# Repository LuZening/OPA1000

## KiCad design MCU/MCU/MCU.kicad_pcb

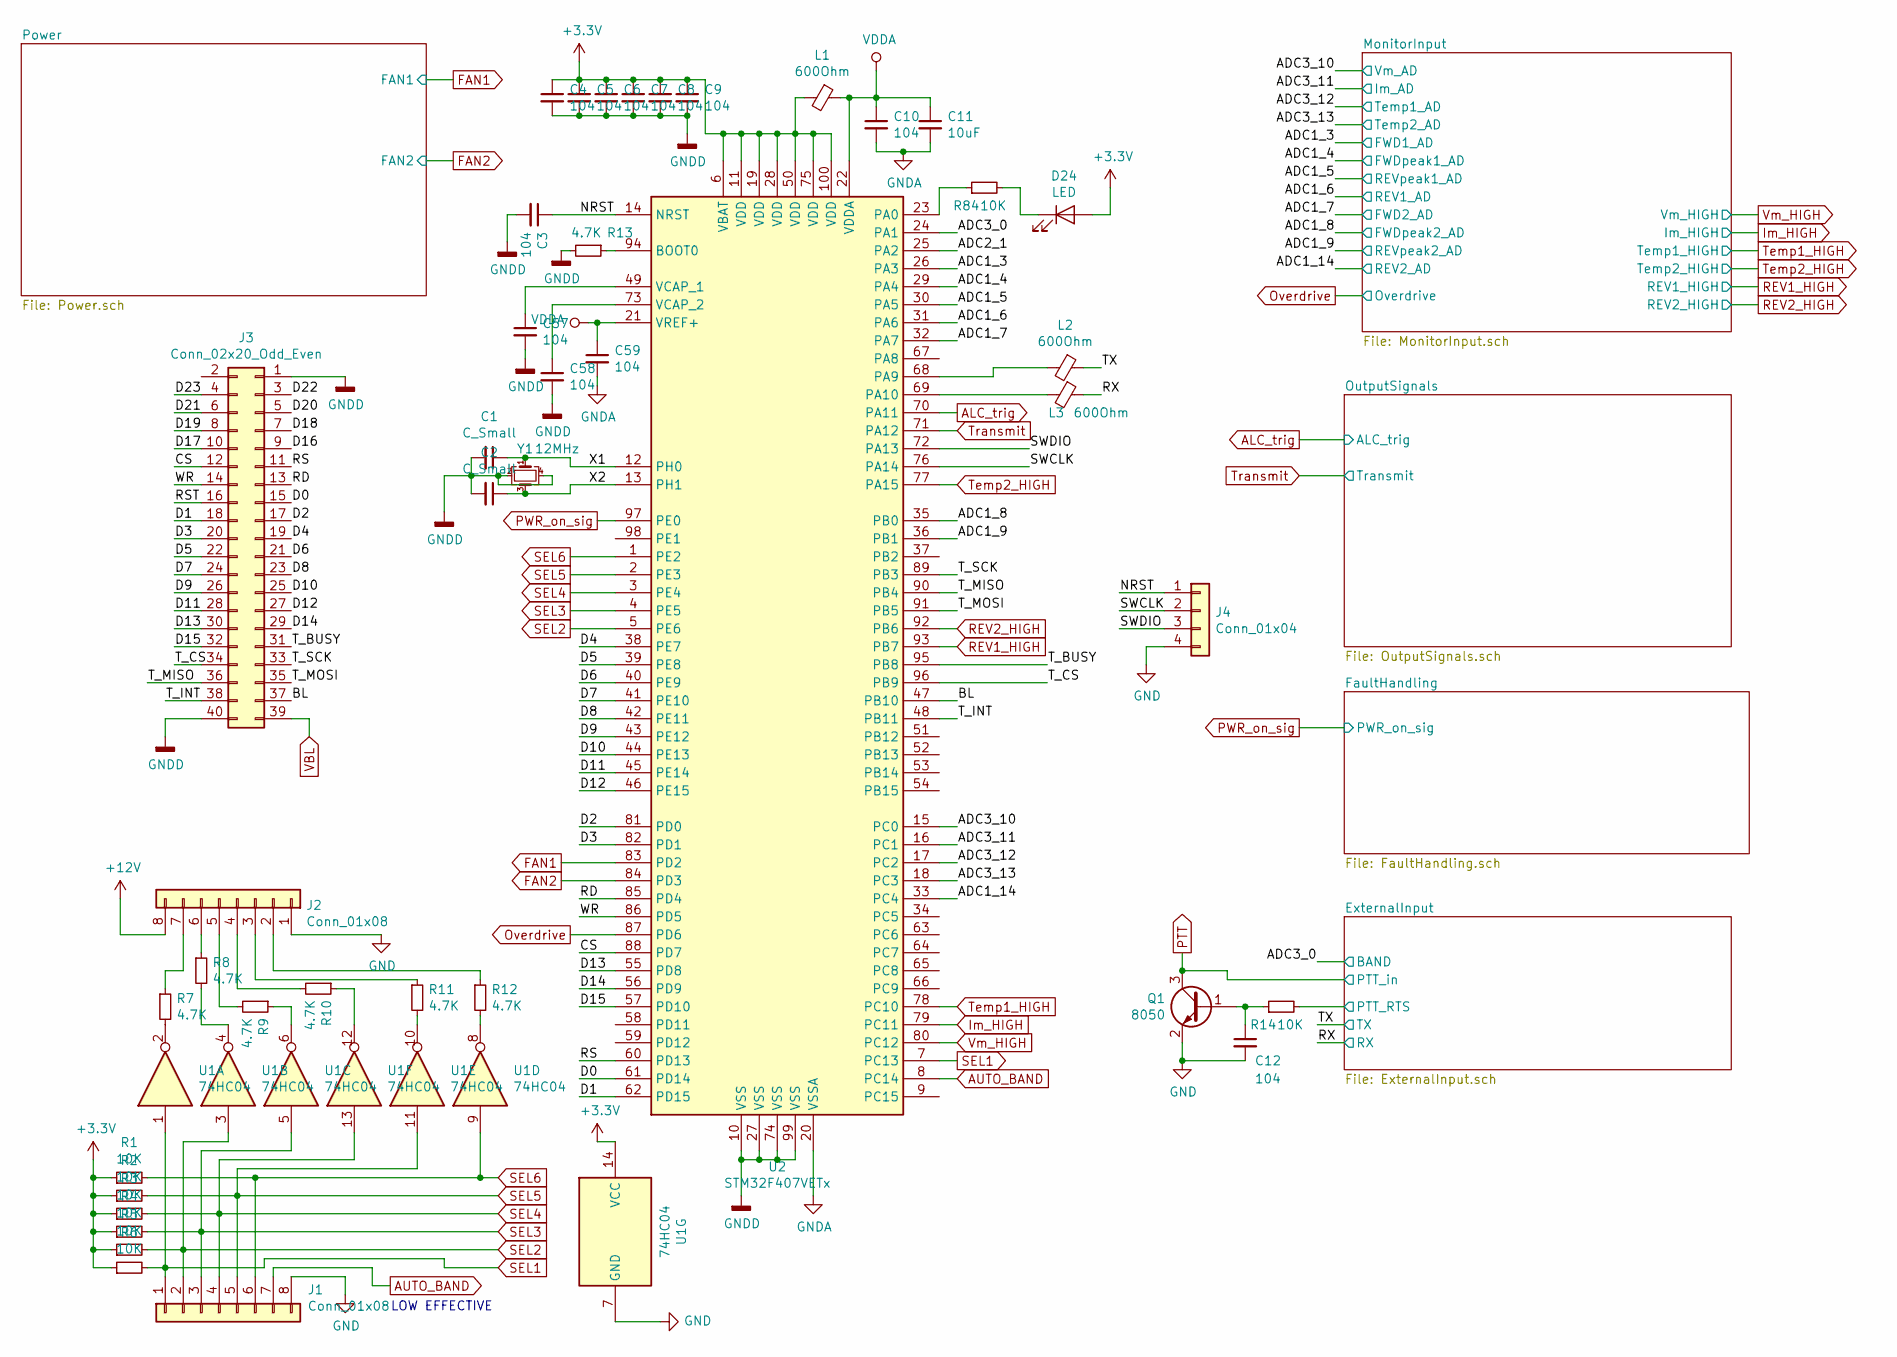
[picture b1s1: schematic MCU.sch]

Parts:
C1, C2: C_Small; C_0805
C3, C4, C5, C6, C7, C8, C9, C10, C12, C57, C58, C59: 104; C_0805
C11: 10uF; C_0805
D24: LED; LED_0805
J1, J2: Conn_01x08; JST_XH_B08B-XH-A_08x2.50mm_Straight
J3: Conn_02x20_Odd_Even; Socket_Strip_Straight_2x20_Pitch2.54mm
J4: Conn_01x04; Pin_Header_Straight_1x04_Pitch2.54mm
L1, L2, L3: 600Ohm; L_0805
Q1: 8050; SOT-23(SOT-23-3)
R1, R2, R3, R4, R5, R6, R14, R84: 10K; R_0805
R7, R8, R9, R10, R11, R12, R13: 4.7K; R_0805
U1: 74HC04; SOIC-14_150MIL
U2: STM32F407VETx; LQFP-100_14X14X05P
Y1: 12MHz; Crystal_SMD_3225-4pin_3.2x2.5mm

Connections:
+3V3: C4.1, C5.1, C6.1, C7.1, C8.1, C9.1, D24.2 (A), L1.2, R1.1, R2.1, R3.1, R4.1, R5.1, R6.1, U1.14 (VCC), U2.6 (VBAT), U2.11 (VDD), U2.19 (VDD), U2.28 (VDD), U2.50 (VDD), U2.75 (VDD), U2.100 (VDD); also elsewhere on the board
+12V: J2.8; also elsewhere on the board
/ADC1_3: U2.26 (PA3); also elsewhere on the board
/ADC1_4: U2.29 (PA4); also elsewhere on the board
/ADC1_5: U2.30 (PA5); also elsewhere on the board
/ADC1_6: U2.31 (PA6); also elsewhere on the board
/ADC1_7: U2.32 (PA7); also elsewhere on the board
/ADC1_8: U2.35 (PB0); also elsewhere on the board
/ADC1_9: U2.36 (PB1); also elsewhere on the board
/ADC1_14: U2.33 (PC4); also elsewhere on the board
/ADC3_1: U2.24 (PA1); also elsewhere on the board
/ADC3_10: U2.15 (PC0); also elsewhere on the board
/ADC3_11: U2.16 (PC1); also elsewhere on the board
/ADC3_12: U2.17 (PC2); also elsewhere on the board
/ADC3_13: U2.18 (PC3); also elsewhere on the board
/BL: J3.37, U2.47 (PB10)
/CAN_RX: U2.51 (PB12); also elsewhere on the board
/CAN_TX: U2.52 (PB13); also elsewhere on the board
/CS: J3.12, U2.88 (PD7)
/D0: J3.15, U2.61 (PD14)
/D1: J3.18, U2.62 (PD15)
/D2: J3.17, U2.81 (PD0)
/D3: J3.20, U2.82 (PD1)
/D4: J3.19, U2.38 (PE7)
/D5: J3.22, U2.39 (PE8)
/D6: J3.21, U2.40 (PE9)
/D7: J3.24, U2.41 (PE10)
/D8: J3.23, U2.42 (PE11)
/D9: J3.26, U2.43 (PE12)
/D10: J3.25, U2.44 (PE13)
/D11: J3.28, U2.45 (PE14)
/D12: J3.27, U2.46 (PE15)
/D13: J3.30, U2.55 (PD8)
/D14: J3.29, U2.56 (PD9)
/D15: J3.32, U2.57 (PD10)
/D16: J3.9
/D17: J3.10
/D18: J3.7
/D19: J3.8
/D20: J3.5
/D21: J3.6
/D22: J3.3
/D23: J3.4
/ExternalInput/PTT_RTS: R14.2; also elsewhere on the board
/MCU_STATE: R84.1, U2.23 (PA0)
/NRST: C3.1, J4.1, U2.14 (NRST)
/RD: J3.13, U2.85 (PD4)
/RESX: J3.16, U2.63 (PC6)
/RS: J3.11, U2.60 (PD13)
/RX: L3.1; also elsewhere on the board
/RX2: U2.87 (PD6)
/SWCLK: J4.2, U2.76 (PA14)
/SWDIO: J4.3, U2.72 (PA13)
/TX: L2.1; also elsewhere on the board
/TX2: U2.25 (PA2)
/T_BUSY: J3.31, U2.95 (PB8)
/T_CS: J3.34, U2.96 (PB9)
/T_INT: J3.38, U2.48 (PB11)
/T_MISO: J3.36, U2.90 (PB4)
/T_MOSI: J3.35, U2.91 (PB5)
/T_SCK: J3.33, U2.89 (PB3)
/WR: J3.14, U2.86 (PD5)
/X1: C1.1, U2.12 (PH0), Y1.1
/X2: C2.1, U2.13 (PH1), Y1.3
ALC_trig: U2.70 (PA11); also elsewhere on the board
AUTO_BAND: J1.7, U2.8 (PC14)
Clear_fault: U2.67 (PA8); also elsewhere on the board
FAN1: U2.83 (PD2); also elsewhere on the board
FAN2: U2.84 (PD3); also elsewhere on the board
Im_HIGH: U2.79 (PC11); also elsewhere on the board
unnamed: C12.1, Q1.1 (B), R14.1
unnamed: C57.1, U2.49 (VCAP_1)
unnamed: C58.1, U2.73 (VCAP_2)
unnamed: D24.1 (K), R84.2
unnamed: J2.2, R12.1
unnamed: J2.3, R11.1
unnamed: J2.4, R10.2
unnamed: J2.5, R9.2
unnamed: J2.6, R8.1
unnamed: J2.7, R7.1
unnamed: L2.2, U2.68 (PA9)
unnamed: L3.2, U2.69 (PA10)
unnamed: R7.2, U1.2
unnamed: R8.2, U1.4
unnamed: R9.1, U1.6
unnamed: R10.1, U1.12
unnamed: R11.2, U1.10
unnamed: R12.2, U1.8
unnamed: R13.1, U2.94 (BOOT0)
Overdrive: U2.98 (PE1); also elsewhere on the board
PTT: Q1.3 (C); also elsewhere on the board
PWR_on_sig: U2.97 (PE0); also elsewhere on the board
REV1_HIGH: U2.93 (PB7); also elsewhere on the board
REV2_HIGH: U2.92 (PB6); also elsewhere on the board
SEL1: J1.1, R6.2, U1.1, U2.7 (PC13)
SEL2: J1.2, R5.2, U1.3, U2.5 (PE6)
SEL3: J1.3, R4.2, U1.5, U2.4 (PE5)
SEL4: J1.4, R3.2, U1.13, U2.3 (PE4)
SEL5: J1.5, R2.2, U1.11, U2.2 (PE3)
SEL6: J1.6, R1.2, U1.9, U2.1 (PE2)
Temp1_HIGH: U2.78 (PC10); also elsewhere on the board
Temp2_HIGH: U2.77 (PA15); also elsewhere on the board
Transmit: U2.71 (PA12); also elsewhere on the board
VBL: J3.39; also elsewhere on the board
VDDA: C10.1, C11.1, C59.1, L1.1, U2.21 (VREF+), U2.22 (VDDA)
Vm_HIGH: U2.80 (PC12); also elsewhere on the board

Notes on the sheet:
LOW EFFECTIVE

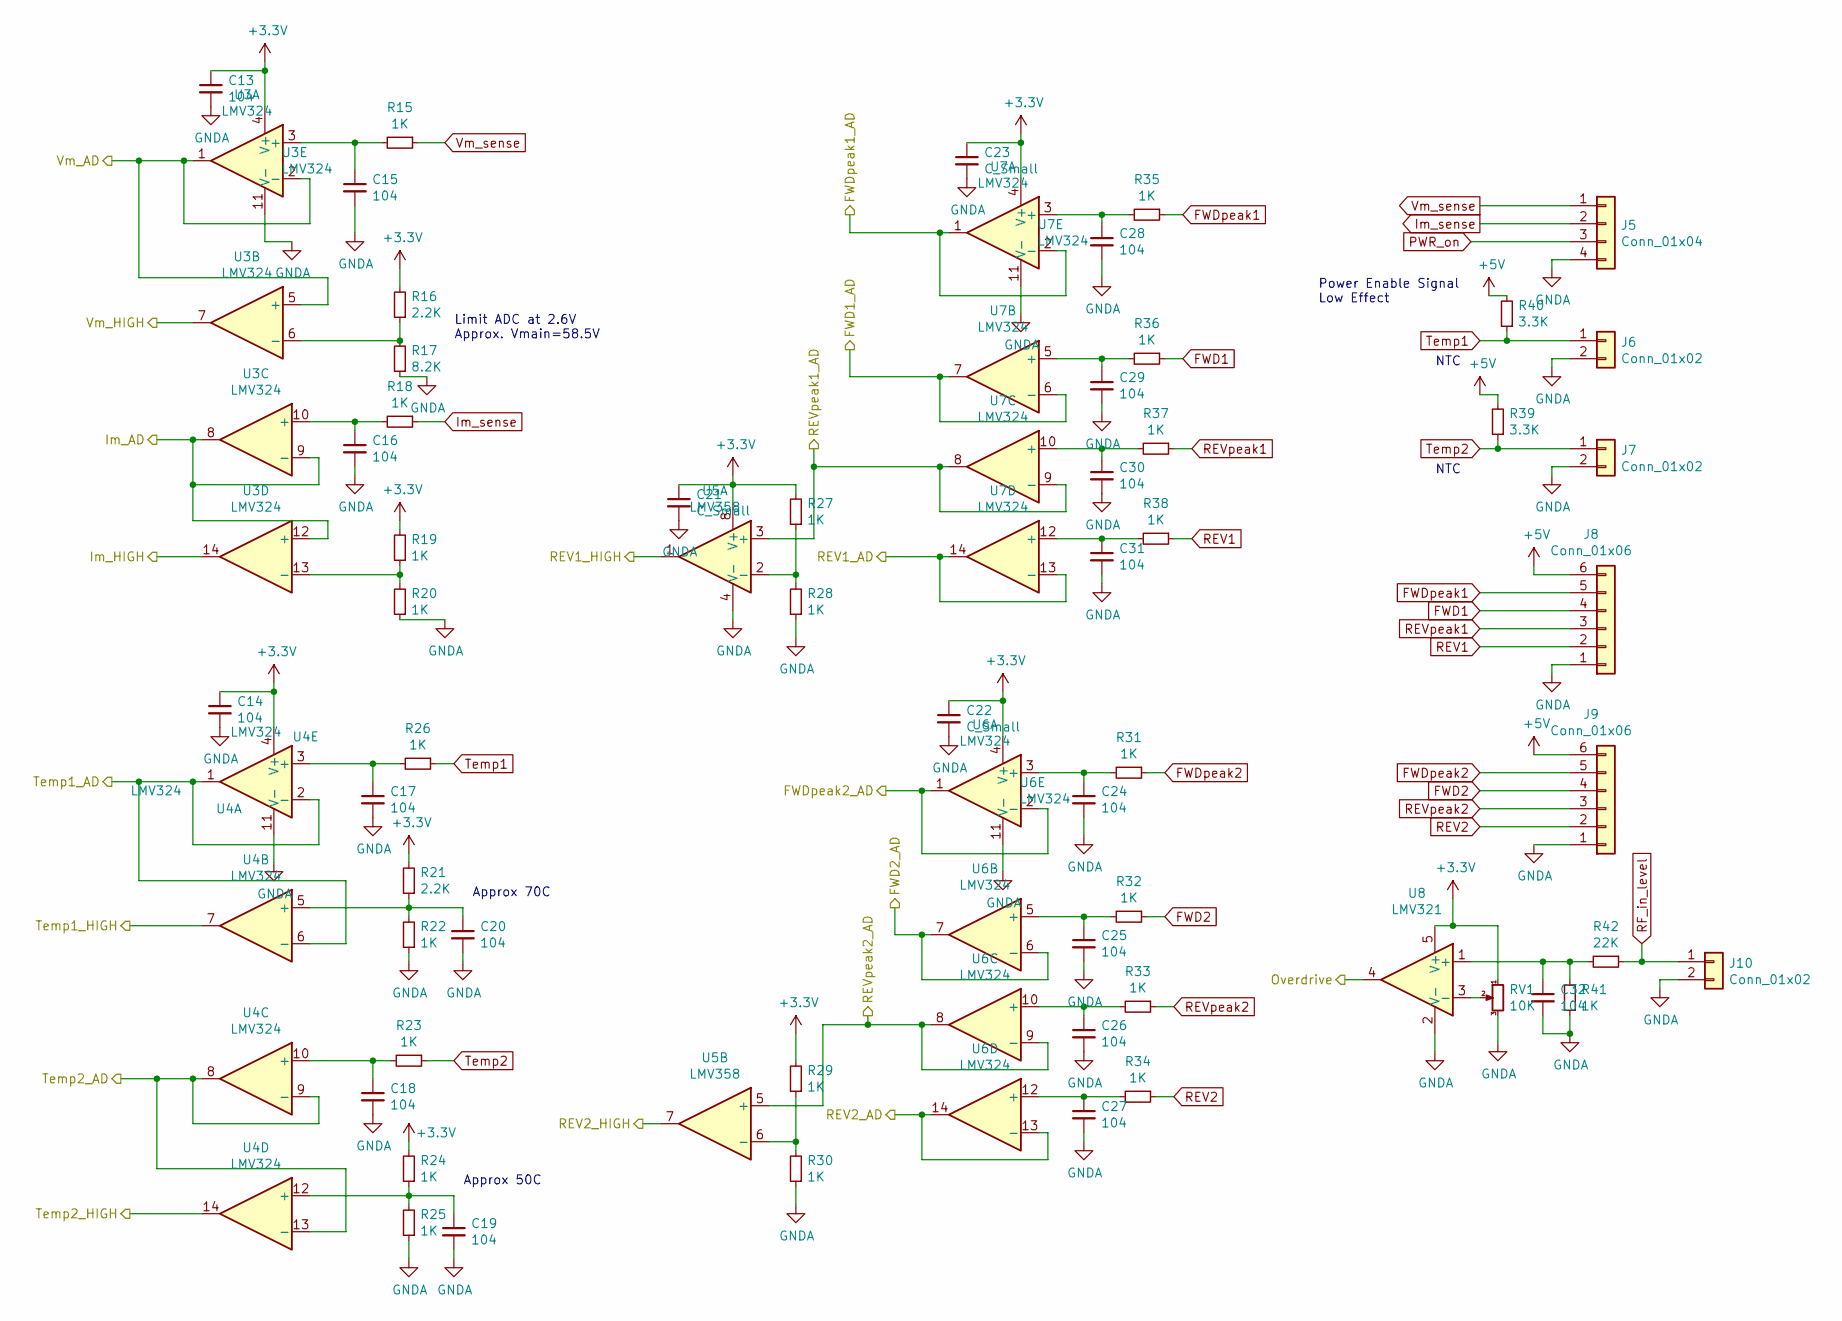
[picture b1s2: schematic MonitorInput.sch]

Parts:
C13, C14, C15, C16, C17, C18, C19, C20, C24, C25, C26, C27, C28, C29, C30, C31, C32: 104; C_0805
C21, C22, C23: C_Small; C_0805
J5: Conn_01x04; JST_XH_B04B-XH-A_04x2.50mm_Straight
J6, J7, J10: Conn_01x02; JST_XH_B02B-XH-A_02x2.50mm_Straight
J8, J9: Conn_01x06; JST_XH_B06B-XH-A_06x2.50mm_Straight
R15, R18, R19, R20, R22, R23, R24, R25, R26, R27, R28, R29, R30, R31, R32, R33, R34, R35, R36, R37, R38, R41: 1K; R_0805
R16, R21: 2.2K; R_0805
R17: 8.2K; R_0805
R39, R40: 3.3K; R_0805
R42: 22K; R_0805
RV1: 10K; 3362P
U3, U4, U6, U7: LMV324; SOIC-14_150MIL
U5: LMV358; SOIC-8_150MIL
U8: LMV321; SOT-23-5

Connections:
+3V3: C13.1, C14.1, C21.1, C22.1, C23.1, R16.2, R19.2, R21.2, R24.2, R27.2, R29.2, RV1.1, U3.4 (V+), U4.4 (V+), U5.8 (V+), U6.4 (V+), U7.4 (V+), U8.5 (V+); also elsewhere on the board
+5V: J8.6, J9.6, R39.2, R40.2; also elsewhere on the board
/ADC1_3: U7.6 (-), U7.7; also elsewhere on the board
/ADC1_4: U7.1, U7.2 (-); also elsewhere on the board
/ADC1_5: U5.3 (+), U7.8, U7.9 (-); also elsewhere on the board
/ADC1_6: U7.13 (-), U7.14; also elsewhere on the board
/ADC1_7: U6.6 (-), U6.7; also elsewhere on the board
/ADC1_8: U6.1, U6.2 (-); also elsewhere on the board
/ADC1_9: U5.5 (+), U6.8, U6.9 (-); also elsewhere on the board
/ADC1_14: U6.13 (-), U6.14; also elsewhere on the board
/ADC3_10: U3.1, U3.2 (-), U3.5 (+); also elsewhere on the board
/ADC3_11: U3.8, U3.9 (-), U3.12 (+); also elsewhere on the board
/ADC3_12: U4.1, U4.2 (-), U4.6 (-); also elsewhere on the board
/ADC3_13: U4.8, U4.9 (-), U4.13 (-); also elsewhere on the board
FWD1: J8.4, R36.1
FWD2: J9.4, R32.1
FWDpeak1: J8.5, R35.1
FWDpeak2: J9.5, R31.1
Im_HIGH: U3.14; also elsewhere on the board
Im_sense: J5.2, R18.1
unnamed: C15.1, R15.2, U3.3 (+)
unnamed: C16.1, R18.2, U3.10 (+)
unnamed: C17.1, R26.2, U4.3 (+)
unnamed: C18.1, R23.2, U4.10 (+)
unnamed: C19.1, R24.1, R25.2, U4.12 (+)
unnamed: C20.1, R21.1, R22.2, U4.5 (+)
unnamed: C24.1, R31.2, U6.3 (+)
unnamed: C25.1, R32.2, U6.5 (+)
unnamed: C26.1, R33.2, U6.10 (+)
unnamed: C27.1, R34.2, U6.12 (+)
unnamed: C28.1, R35.2, U7.3 (+)
unnamed: C29.1, R36.2, U7.5 (+)
unnamed: C30.1, R37.2, U7.10 (+)
unnamed: C31.1, R38.2, U7.12 (+)
unnamed: C32.1, R41.2, R42.2, U8.1 (+)
unnamed: R16.1, R17.2, U3.6 (-)
unnamed: R19.1, R20.2, U3.13 (-)
unnamed: R27.1, R28.2, U5.2 (-)
unnamed: R29.1, R30.2, U5.6 (-)
unnamed: RV1.2, U8.3 (-)
Overdrive: U8.4; also elsewhere on the board
PWR_on: J5.3; also elsewhere on the board
REV1: J8.2, R38.1
REV1_HIGH: U5.1; also elsewhere on the board
REV2: J9.2, R34.1
REV2_HIGH: U5.7; also elsewhere on the board
REVpeak1: J8.3, R37.1
REVpeak2: J9.3, R33.1
RF_in_level: J10.1, R42.1
Temp1: J6.1, R26.1, R40.1
Temp1_HIGH: U4.7; also elsewhere on the board
Temp2: J7.1, R23.1, R39.1
Temp2_HIGH: U4.14; also elsewhere on the board
Vm_HIGH: U3.7; also elsewhere on the board
Vm_sense: J5.1, R15.1

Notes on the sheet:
Power Enable Signal Low Effect
NTC
Approx 70C
Approx 50C
Limit ADC at 2.6V Approx. Vmain=58.5V

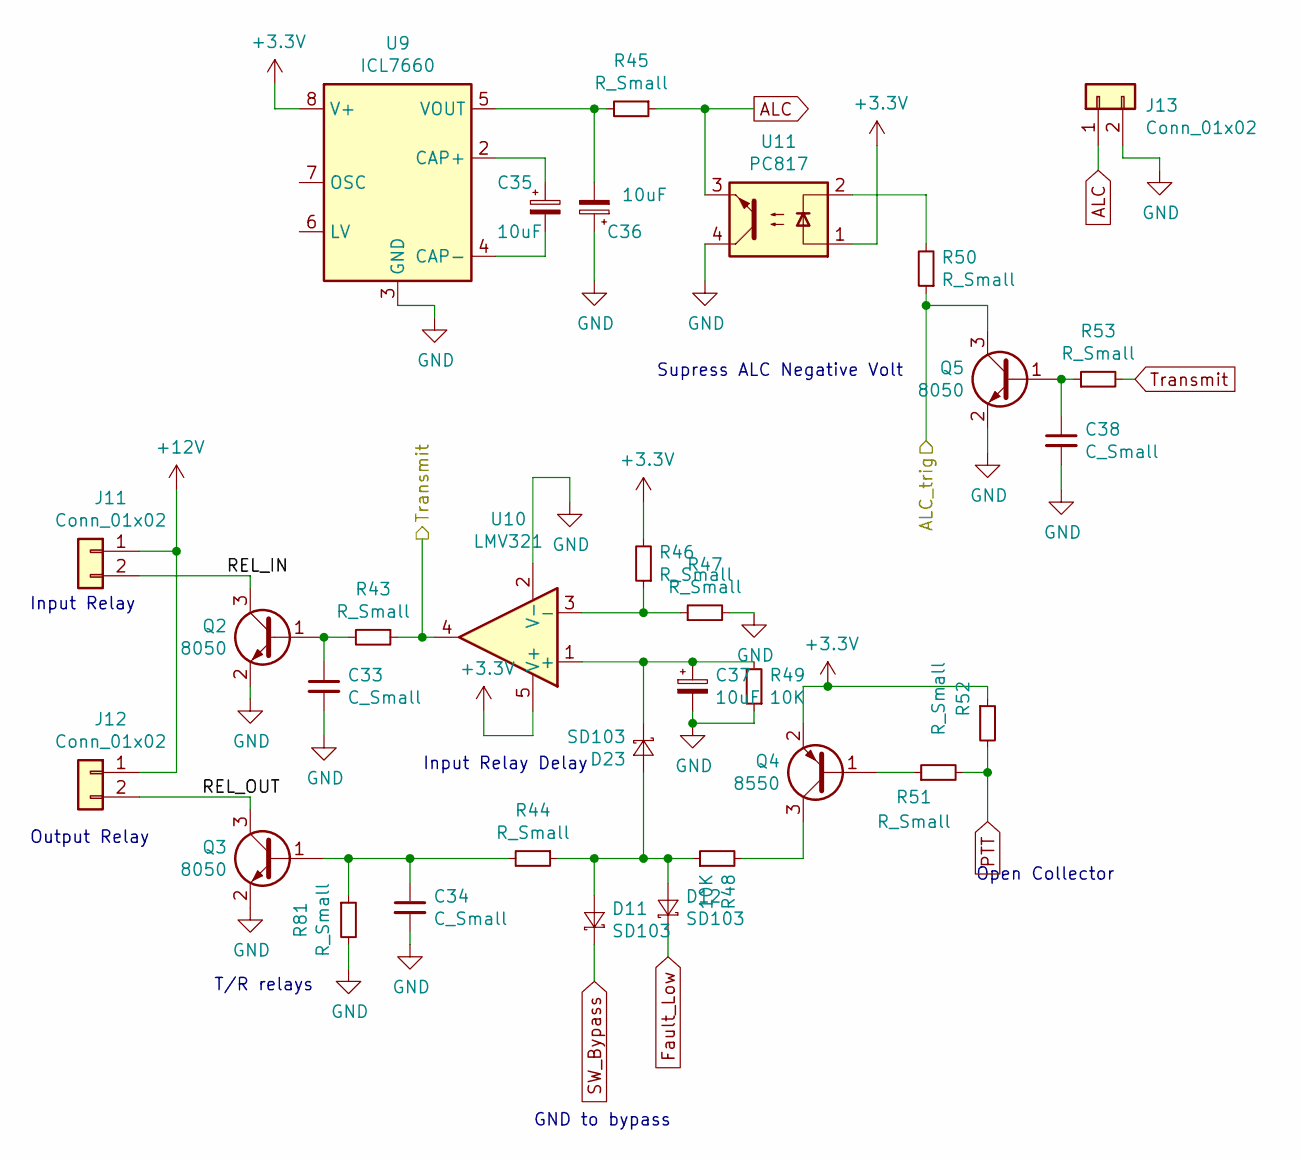
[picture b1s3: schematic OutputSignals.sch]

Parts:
C33, C34, C38: C_Small; C_0805
C35, C36, C37: 10uF; C_0805
D11, D12, D23: SD103; SOD-123
J11, J12: Conn_01x02; JST_XH_B02B-XH-A_02x2.50mm_Straight
J13: Conn_01x02; Pin_Header_Straight_1x02_Pitch2.54mm
Q2, Q3, Q5: 8050; SOT-23(SOT-23-3)
Q4: 8550; SOT-23(SOT-23-3)
R43, R44, R45, R46, R47, R50, R51, R52, R53, R81: R_Small; R_0805
R48, R49: 10K; R_0805
U9: ICL7660; SOIC-8_150MIL
U10: LMV321; SOT-23-5
U11: PC817; DIP-4

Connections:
+3V3: Q4.2 (E), R46.2, R52.1, U9.8 (V+), U10.5 (V+), U11.1; also elsewhere on the board
+12V: J11.1, J12.1; also elsewhere on the board
/OutputSignals/REL_IN: J11.2, Q2.3 (C)
/OutputSignals/REL_OUT: J12.2, Q3.3 (C)
ALC: J13.1, R45.1, U11.3
ALC_trig: Q5.3 (C), R50.1; also elsewhere on the board
Fault_Low: D12.2 (K); also elsewhere on the board
unnamed 86: C38.1, Q5.1 (B), R53.1; also elsewhere on the board
unnamed: C33.1, Q2.1 (B), R43.2
unnamed: C35.1, U9.2 (CAP+)
unnamed: C35.2, U9.4 (CAP-)
unnamed: C36.2, R45.2, U9.5 (VOUT)
unnamed: C37.1, D23.2 (K), R49.2, U10.1 (+)
unnamed: Q4.1 (B), R51.1
unnamed: Q4.3 (C), R48.2
unnamed: R46.1, R47.1, U10.3 (-)
unnamed: R50.2, U11.2
PTT: R51.2, R52.2; also elsewhere on the board
SW_Bypass: D11.2 (K); also elsewhere on the board
Transmit: R43.1, U10.4; also elsewhere on the board

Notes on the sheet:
T/R relays
GND to bypass
Output Relay
Input Relay
Input Relay Delay
Supress ALC Negative Volt
Open Collector

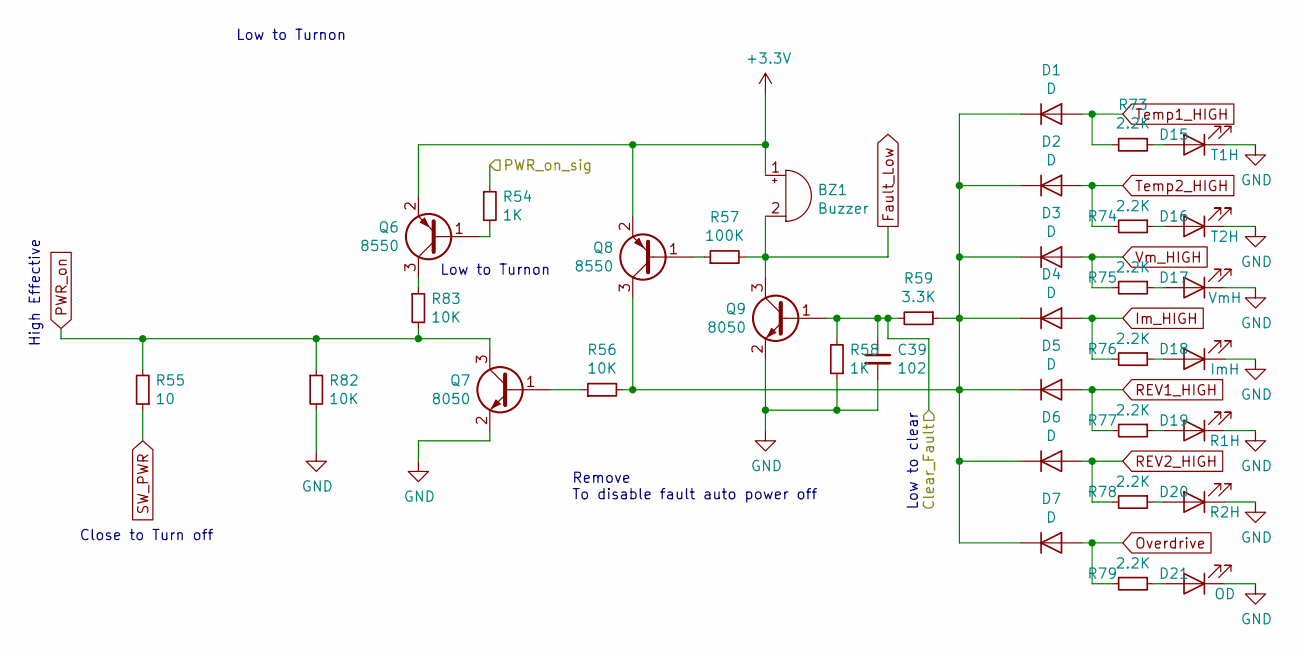
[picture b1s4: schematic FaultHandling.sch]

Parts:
BZ1: Buzzer; Buzzer_12x9.5RM7.6
C39: 102; C_0805
D1, D2, D3, D4, D5, D6, D7: D; LL-34
D15: T1H; LED_0805
D16: T2H; LED_0805
D17: VmH; LED_0805
D18: ImH; LED_0805
D19: R1H; LED_0805
D20: R2H; LED_0805
D21: OD; LED_0805
Q6, Q8: 8550; SOT-23(SOT-23-3)
Q7, Q9: 8050; SOT-23(SOT-23-3)
R54, R58: 1K; R_0805
R55: 10; R_0805
R56, R82, R83: 10K; R_0805
R57: 100K; R_0805
R59: 3.3K; R_0805
R73, R74, R75, R76, R77, R78, R79: 2.2K; R_0805

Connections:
+3V3: BZ1.1 (-), Q6.2 (E), Q8.2 (E); also elsewhere on the board
/FaultHandling/Clear_Fault: C39.1, Q9.1 (B), R58.2, R59.2; also elsewhere on the board
Fault_Low: BZ1.2 (+), Q9.3 (C), R57.2; also elsewhere on the board
Im_HIGH: D4.1 (A), R76.2; also elsewhere on the board
unnamed: D1.2 (K), D2.2 (K), D3.2 (K), D4.2 (K), D5.2 (K), D6.2 (K), D7.2 (K), Q8.3 (C), R56.2, R59.1
unnamed: D15.2 (A), R73.1
unnamed: D16.2 (A), R74.1
unnamed: D17.2 (A), R75.1
unnamed: D18.2 (A), R76.1
unnamed: D19.2 (A), R77.1
unnamed: D20.2 (A), R78.1
unnamed: D21.2 (A), R79.1
unnamed: Q6.1 (B), R54.2
unnamed: Q6.3 (C), R83.1
unnamed: Q7.1 (B), R56.1
unnamed: Q8.1 (B), R57.1
Overdrive: D7.1 (A), R79.2; also elsewhere on the board
PWR_on: Q7.3 (C), R55.2, R82.1, R83.2; also elsewhere on the board
PWR_on_sig: R54.1; also elsewhere on the board
REV1_HIGH: D5.1 (A), R77.2; also elsewhere on the board
REV2_HIGH: D6.1 (A), R78.2; also elsewhere on the board
SW_PWR: R55.1; also elsewhere on the board
Temp1_HIGH: D1.1 (A), R73.2; also elsewhere on the board
Temp2_HIGH: D2.1 (A), R74.2; also elsewhere on the board
Vm_HIGH: D3.1 (A), R75.2; also elsewhere on the board

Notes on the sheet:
Low to Turnon
High Effective
Close to Turn off
Low to clear
Remove To disable fault auto power off

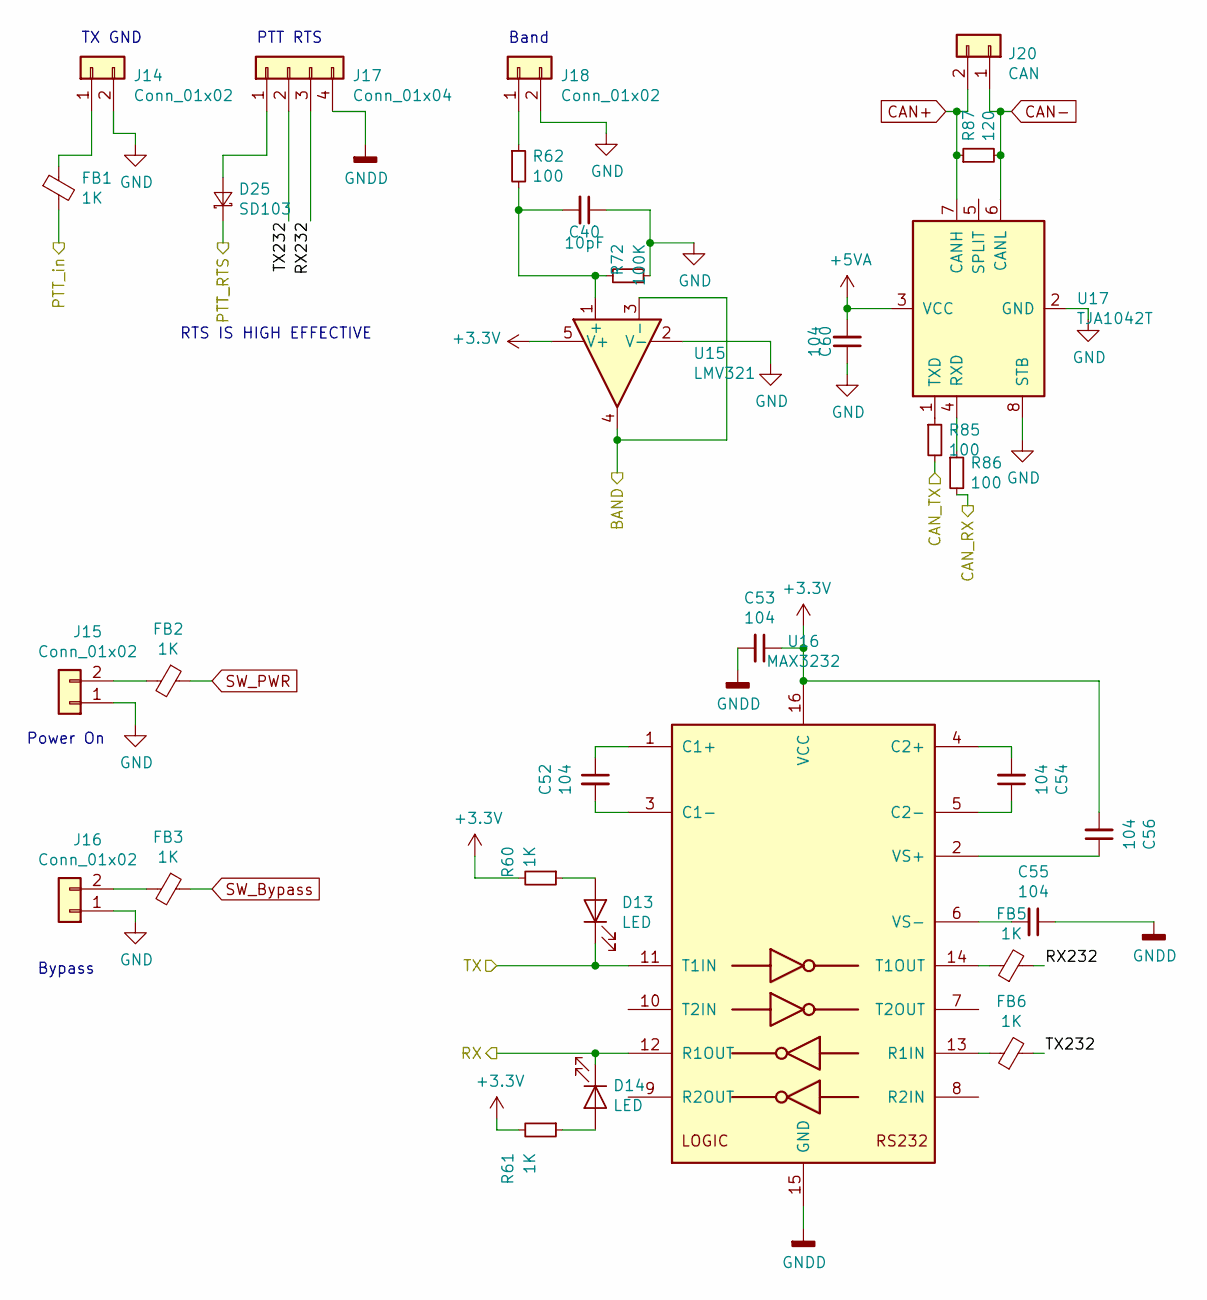
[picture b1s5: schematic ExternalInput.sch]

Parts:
C40: 10pF; C_0805
C52, C53, C54, C55, C56, C60: 104; C_0805
D13, D14: LED; LED_0805
D25: SD103; SOD-123
FB1, FB2, FB3, FB5, FB6: 1K; R_0805
J14, J15, J16, J18: Conn_01x02; Pin_Header_Straight_1x02_Pitch2.54mm
J17: Conn_01x04; JST_XH_B04B-XH-A_04x2.50mm_Straight
J20: CAN; JST_XH_B02B-XH-A_02x2.50mm_Straight
R60, R61: 1K; R_0805
R62, R85, R86: 100; R_0805
R72: 100K; R_0805
R87: 120; R_0805
U15: LMV321; SOT-23-5
U16: MAX3232; SOIC-16_150MIL
U17: TJA1042T; SOIC-8_150MIL

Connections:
+3V3: C53.1, C56.2, R60.2, R61.2, U15.5 (V+), U16.16 (VCC); also elsewhere on the board
+5VA: C60.2, U17.3 (VCC); also elsewhere on the board
/ADC3_1: U15.3 (-), U15.4; also elsewhere on the board
/CAN_RX: R86.2; also elsewhere on the board
/CAN_TX: R85.2; also elsewhere on the board
/ExternalInput/PTT_RTS: D25.2 (K); also elsewhere on the board
/ExternalInput/RX232: FB5.2, J17.3
/ExternalInput/TX232: FB6.2, J17.2
/RX: D14.1 (K), U16.12 (R1OUT); also elsewhere on the board
/TX: D13.1 (K), U16.11 (T1IN); also elsewhere on the board
CAN+: J20.2, R87.1, U17.7 (CANH)
CAN-: J20.1, R87.2, U17.6 (CANL)
unnamed: C40.2, R62.2, R72.2, U15.1 (+)
unnamed: C52.1, U16.1 (C1+)
unnamed: C52.2, U16.3 (C1-)
unnamed: C54.1, U16.5 (C2-)
unnamed: C54.2, U16.4 (C2+)
unnamed: C55.2, U16.6 (VS-)
unnamed: C56.1, U16.2 (VS+)
unnamed: D13.2 (A), R60.1
unnamed: D14.2 (A), R61.1
unnamed: D25.1 (A), J17.1
unnamed: FB1.1, J14.1
unnamed: FB2.2, J15.2
unnamed: FB3.2, J16.2
unnamed: FB5.1, U16.14 (T1OUT)
unnamed: FB6.1, U16.13 (R1IN)
unnamed: J18.1, R62.1
unnamed: R85.1, U17.1 (TXD)
unnamed: R86.1, U17.4 (RXD)
PTT: FB1.2; also elsewhere on the board
SW_Bypass: FB3.1; also elsewhere on the board
SW_PWR: FB2.1; also elsewhere on the board

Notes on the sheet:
Power On
Bypass
TX GND
PTT RTS
Band
RTS IS HIGH EFFECTIVE

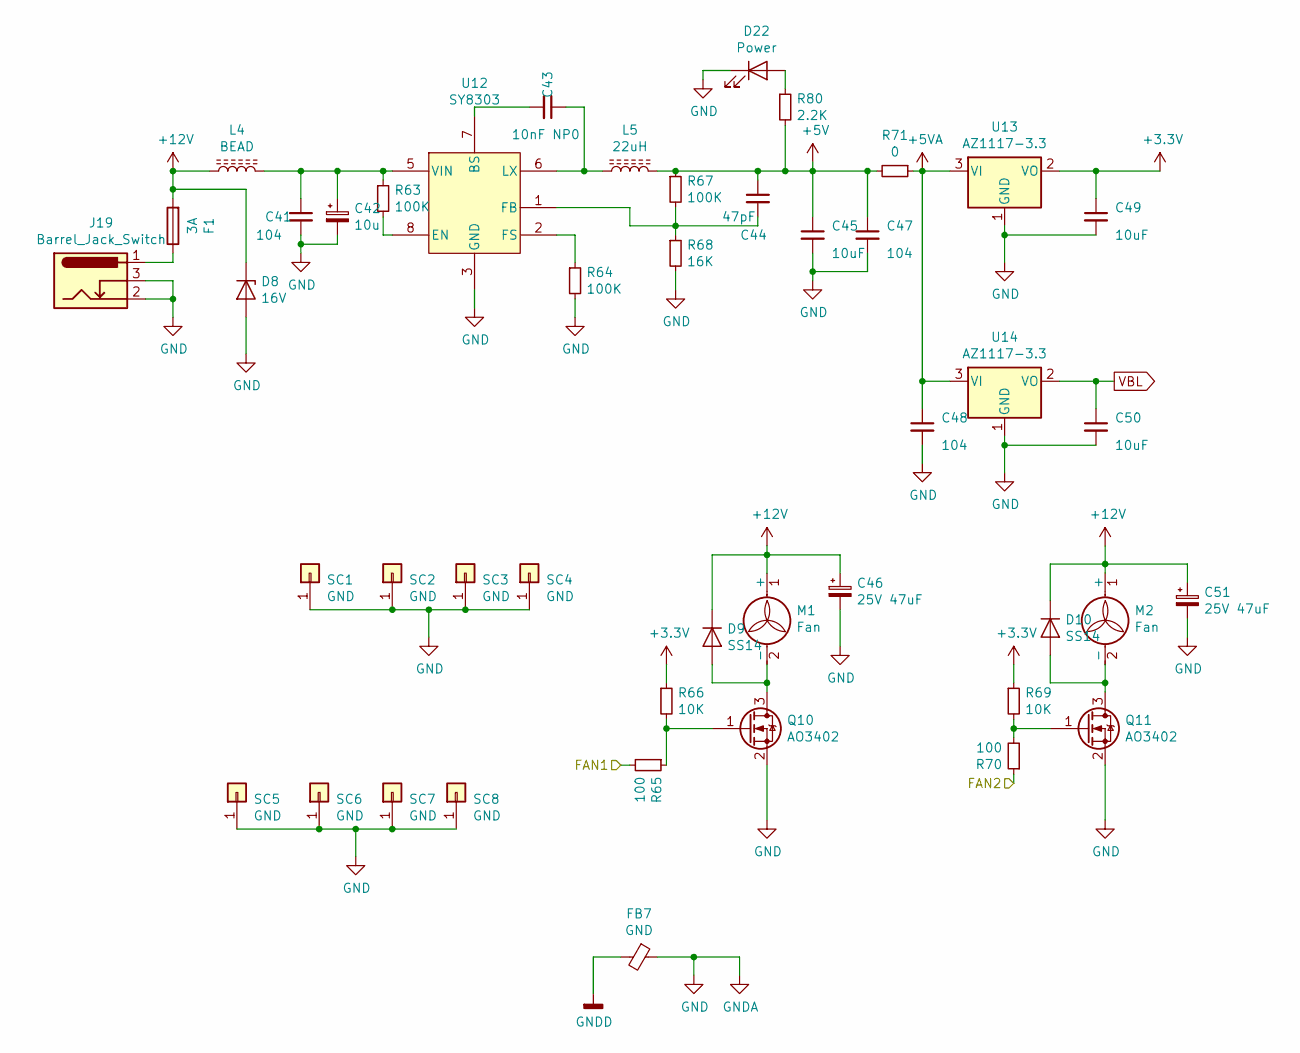
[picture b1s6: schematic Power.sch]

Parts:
C41, C47, C48: 104; C_0805
C42: 10u; CP_Radial_D5.0mm_P2.50mm
C43: 10nF NP0; C_0805
C44: 47pF; C_0805
C45, C49, C50: 10uF; C_0805
C46, C51: 25V 47uF; CP_Radial_D5.0mm_P2.50mm
D8: 16V; LL-34
D9, D10: SS14; SMA(DO-214AC)_S1
D22: Power; LED_0805
F1: 3A; R_1206
FB7: GND; R_1206
J19: Barrel_Jack_Switch; BARREL_JACK
L4: BEAD; L_1206
L5: 22uH; L_SMD4030_hand
M1, M2: Fan; JST_XH_B02B-XH-A_02x2.50mm_Straight
Q10, Q11: AO3402; SOT-23(SOT-23-3)
R63, R64, R67: 100K; R_0805
R65, R70: 100; R_0805
R66, R69: 10K; R_0805
R68: 16K; R_0805
R71: 0; R_1206
R80: 2.2K; R_0805
SC1, SC2, SC3, SC4, SC5, SC6, SC7, SC8: GND; M3_Screwhole
U12: SY8303; TSOT-23-8_HandSoldering
U13, U14: AZ1117-3.3; SOT-223

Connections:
+3V3: C49.1, R66.1, R69.1, U13.2 (VO); also elsewhere on the board
+5V: C44.1, C45.1, C47.1, L5.2, R67.1, R71.2, R80.2; also elsewhere on the board
+5VA: C48.1, R71.1, U13.3 (VI), U14.3 (VI); also elsewhere on the board
+12V: C46.1, C51.1, D8.2 (K), D9.2 (K), D10.2 (K), F1.2, L4.1, M1.1 (+), M2.1 (+); also elsewhere on the board
FAN1: R65.2; also elsewhere on the board
FAN2: R70.1; also elsewhere on the board
unnamed: C41.1, C42.1, L4.2, R63.1, U12.5 (VIN)
unnamed: C43.1, L5.1, U12.6 (LX)
unnamed: C43.2, U12.7 (BS)
unnamed: C44.2, R67.2, R68.1, U12.1 (FB)
unnamed: D9.1 (A), M1.2 (-), Q10.3 (D)
unnamed: D10.1 (A), M2.2 (-), Q11.3 (D)
unnamed: D22.2 (A), R80.1
unnamed: F1.1, J19.1
unnamed: Q10.1 (G), R65.1, R66.2
unnamed: Q11.1 (G), R69.2, R70.2
unnamed: R63.2, U12.8 (EN)
unnamed: R64.1, U12.2 (FS)
VBL: C50.1, U14.2 (VO); also elsewhere on the board

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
